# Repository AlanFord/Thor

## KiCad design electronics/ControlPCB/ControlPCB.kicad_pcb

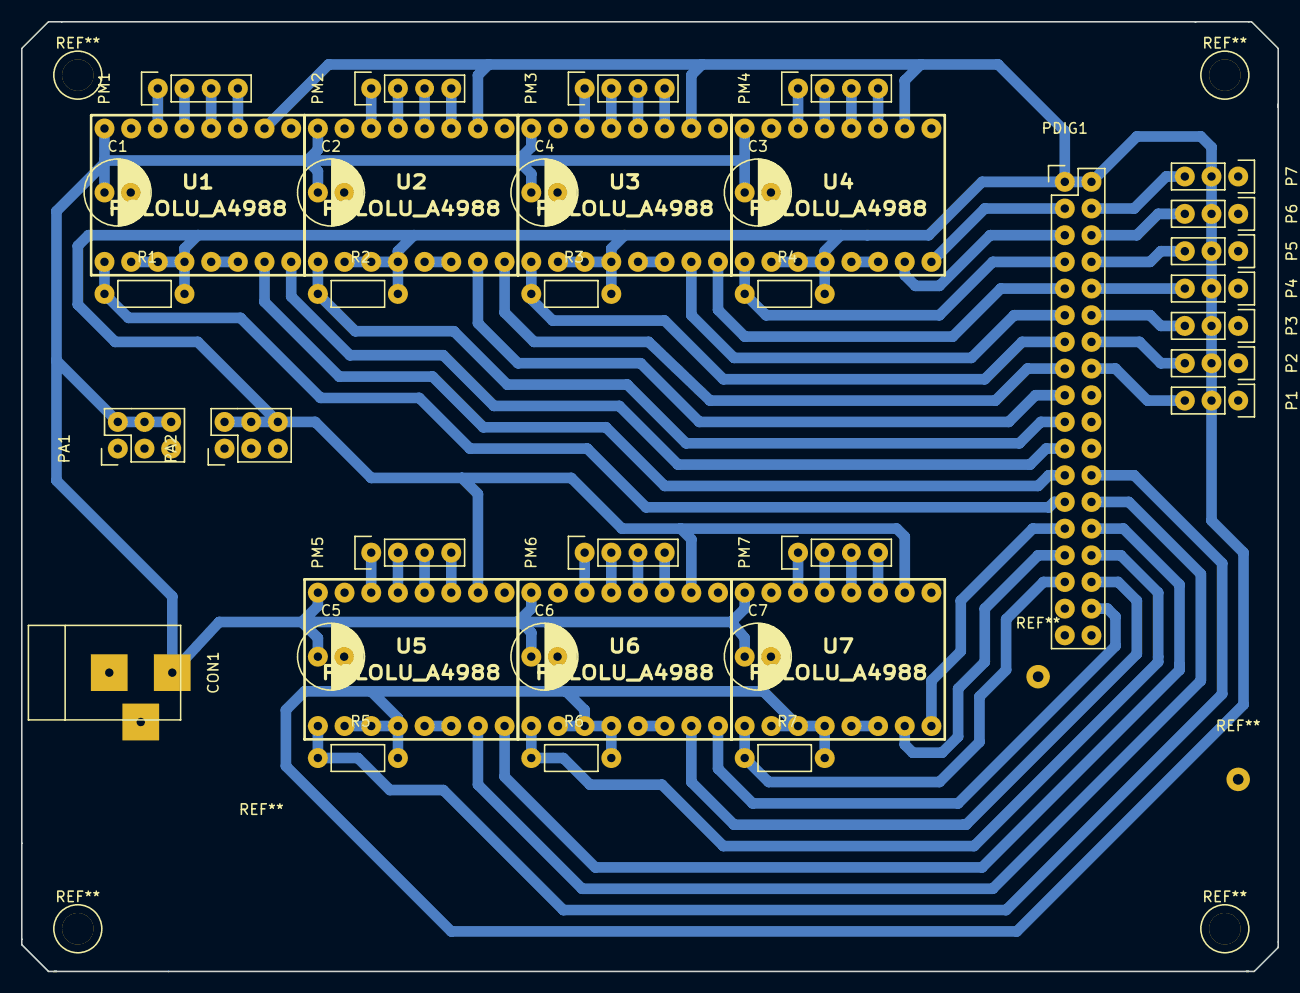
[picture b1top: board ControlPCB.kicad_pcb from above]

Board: 2 copper layers, 119.6 x 90.4 mm, 39 parts (0 on the bottom side), 66 nets.

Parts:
C1, C2, C3, C4, C5, C6, C7: CP1_Small; C_Radial_D6.3_L11.2_P2.5THOR
CON1: 12VINPUT; BARREL_JACK
P1: Opto1; Pin_Header_Straight_1x03
P2: Opto2; Pin_Header_Straight_1x03
P3: Opto3; Pin_Header_Straight_1x03
P4: Opto4; Pin_Header_Straight_1x03
P5: Opto5; Pin_Header_Straight_1x03
P6: Opto6; Pin_Header_Straight_1x03
P7: Tool; Pin_Header_Straight_1x03
PA1: AUX12V; Pin_Header_Straight_2x03
PA2: AUX5V; Pin_Header_Straight_2x03
PDIG1: CONN_02X18; Pin_Header_Straight_2x18
PM1, PM2, PM3, PM4, PM5, PM6, PM7: CONN_01X04; Pin_Header_Straight_1x04
R1, R2, R3, R4, R5, R6, R7: R; Resistor_Horizontal_RM7mm
U1, U2, U3, U4, U5, U6, U7: POLOLU_A4988; POLA4988

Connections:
1AM1: PM1.3, U1.4
1AM2: PM2.3, U2.4
1AM3: PM3.3, U3.4
1AM4: PM4.3, U4.4
1AM5: PM5.3, U5.4
1AM6: PM6.3, U6.4
1AM7: PM7.3, U7.4
1BM1: PM1.4, U1.3
1BM2: PM2.4, U2.3
1BM3: PM3.4, U3.3
1BM4: PM4.4, U4.3
1BM5: PM5.4, U5.3
1BM6: PM6.4, U6.3
1BM7: PM7.4, U7.3
2AM1: PM1.2, U1.5
2AM2: PM2.2, U2.5
2AM3: PM3.2, U3.5
2AM4: PM4.2, U4.5
2AM5: PM5.2, U5.5
2AM6: PM6.2, U6.5
2AM7: PM7.2, U7.5
2BM1: PM1.1, U1.6
2BM2: PM2.1, U2.6
2BM3: PM3.1, U3.6
2BM4: PM4.1, U4.6
2BM5: PM5.1, U5.6
2BM6: PM6.1, U6.6
2BM7: PM7.1, U7.6
+12V: C1.1, C2.1, C3.1, C4.1, C5.1, C6.1, C7.1, CON1.1, PA1.2, PA1.4, PA1.6, U1.8, U2.8, U3.8, U4.8, U5.8, U6.8, U7.8
DIRM1: PDIG1.21, U1.16
DIRM2: PDIG1.15, U2.16
DIRM3: PDIG1.9, U3.16
DIRM4: PDIG1.3, U4.16
DIRM5: PDIG1.28, U5.16
DIRM6: PDIG1.34, U6.16
DIRM7: PDIG1.27, U7.16
ENABLEM1: PDIG1.25, R1.1, U1.9
ENABLEM2: PDIG1.19, R2.1, U2.9
ENABLEM3: PDIG1.13, R3.1, U3.9
ENABLEM4: PDIG1.7, R4.1, U4.9
ENABLEM5: PDIG1.24, R5.1, U5.9
ENABLEM6: PDIG1.30, R6.1, U6.9
ENABLEM7: PDIG1.31, R7.1, U7.9
GND: C1.2, C2.2, C3.2, C4.2, C5.2, C6.2, C7.2, CON1.2, CON1.3, P1.1, P2.1, P3.1, P4.1, P5.1, P6.1, P7.1, PA1.1, PA1.3, PA1.5, PA2.1, PA2.3, PA2.5, PDIG1.35, PDIG1.36, U1.1, U1.7, U2.1, U2.7, U3.1, U3.7, U4.1, U4.7, U5.1, U5.7, U6.1, U6.7, U7.1, U7.7
unnamed: U1.13, U1.14
unnamed: U2.13, U2.14
unnamed: U3.13, U3.14
unnamed: U4.13, U4.14
unnamed: U5.13, U5.14
unnamed: U6.13, U6.14
unnamed: U7.13, U7.14
SOPTO1: P1.3, PDIG1.16
SOPTO2: P2.3, PDIG1.14
SOPTO3: P3.3, PDIG1.12
SOPTO4: P4.3, PDIG1.10
SOPTO5: P5.3, PDIG1.8
SOPTO6: P6.3, PDIG1.6
STEPM1: PDIG1.23, U1.15
STEPM2: PDIG1.17, U2.15
STEPM3: PDIG1.11, U3.15
STEPM4: PDIG1.5, U4.15
STEPM5: PDIG1.26, U5.15
STEPM6: PDIG1.32, U6.15
STEPM7: PDIG1.29, U7.15
STOOL: P7.3, PDIG1.4
VCC: P1.2, P2.2, P3.2, P4.2, P5.2, P6.2, P7.2, PA2.2, PA2.4, PA2.6, PDIG1.1, PDIG1.2, R1.2, R2.2, R3.2, R4.2, R5.2, R6.2, R7.2, U1.2, U1.10, U1.11, U1.12, U2.2, U2.10, U2.11, U2.12, U3.2, U3.10, U3.11, U3.12, U4.2, U4.10, U4.11, U4.12, U5.2, U5.10, U5.11, U5.12, U6.2, U6.10, U6.11, U6.12, U7.2, U7.10, U7.11, U7.12

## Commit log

2016-12-19 added attachment points to jumper ground net to isolated fill area
2016-12-19 added auxiliary axis
2016-12-19 added thermal relief to copper files and generated svg for milling
2016-12-19 generated drill map
